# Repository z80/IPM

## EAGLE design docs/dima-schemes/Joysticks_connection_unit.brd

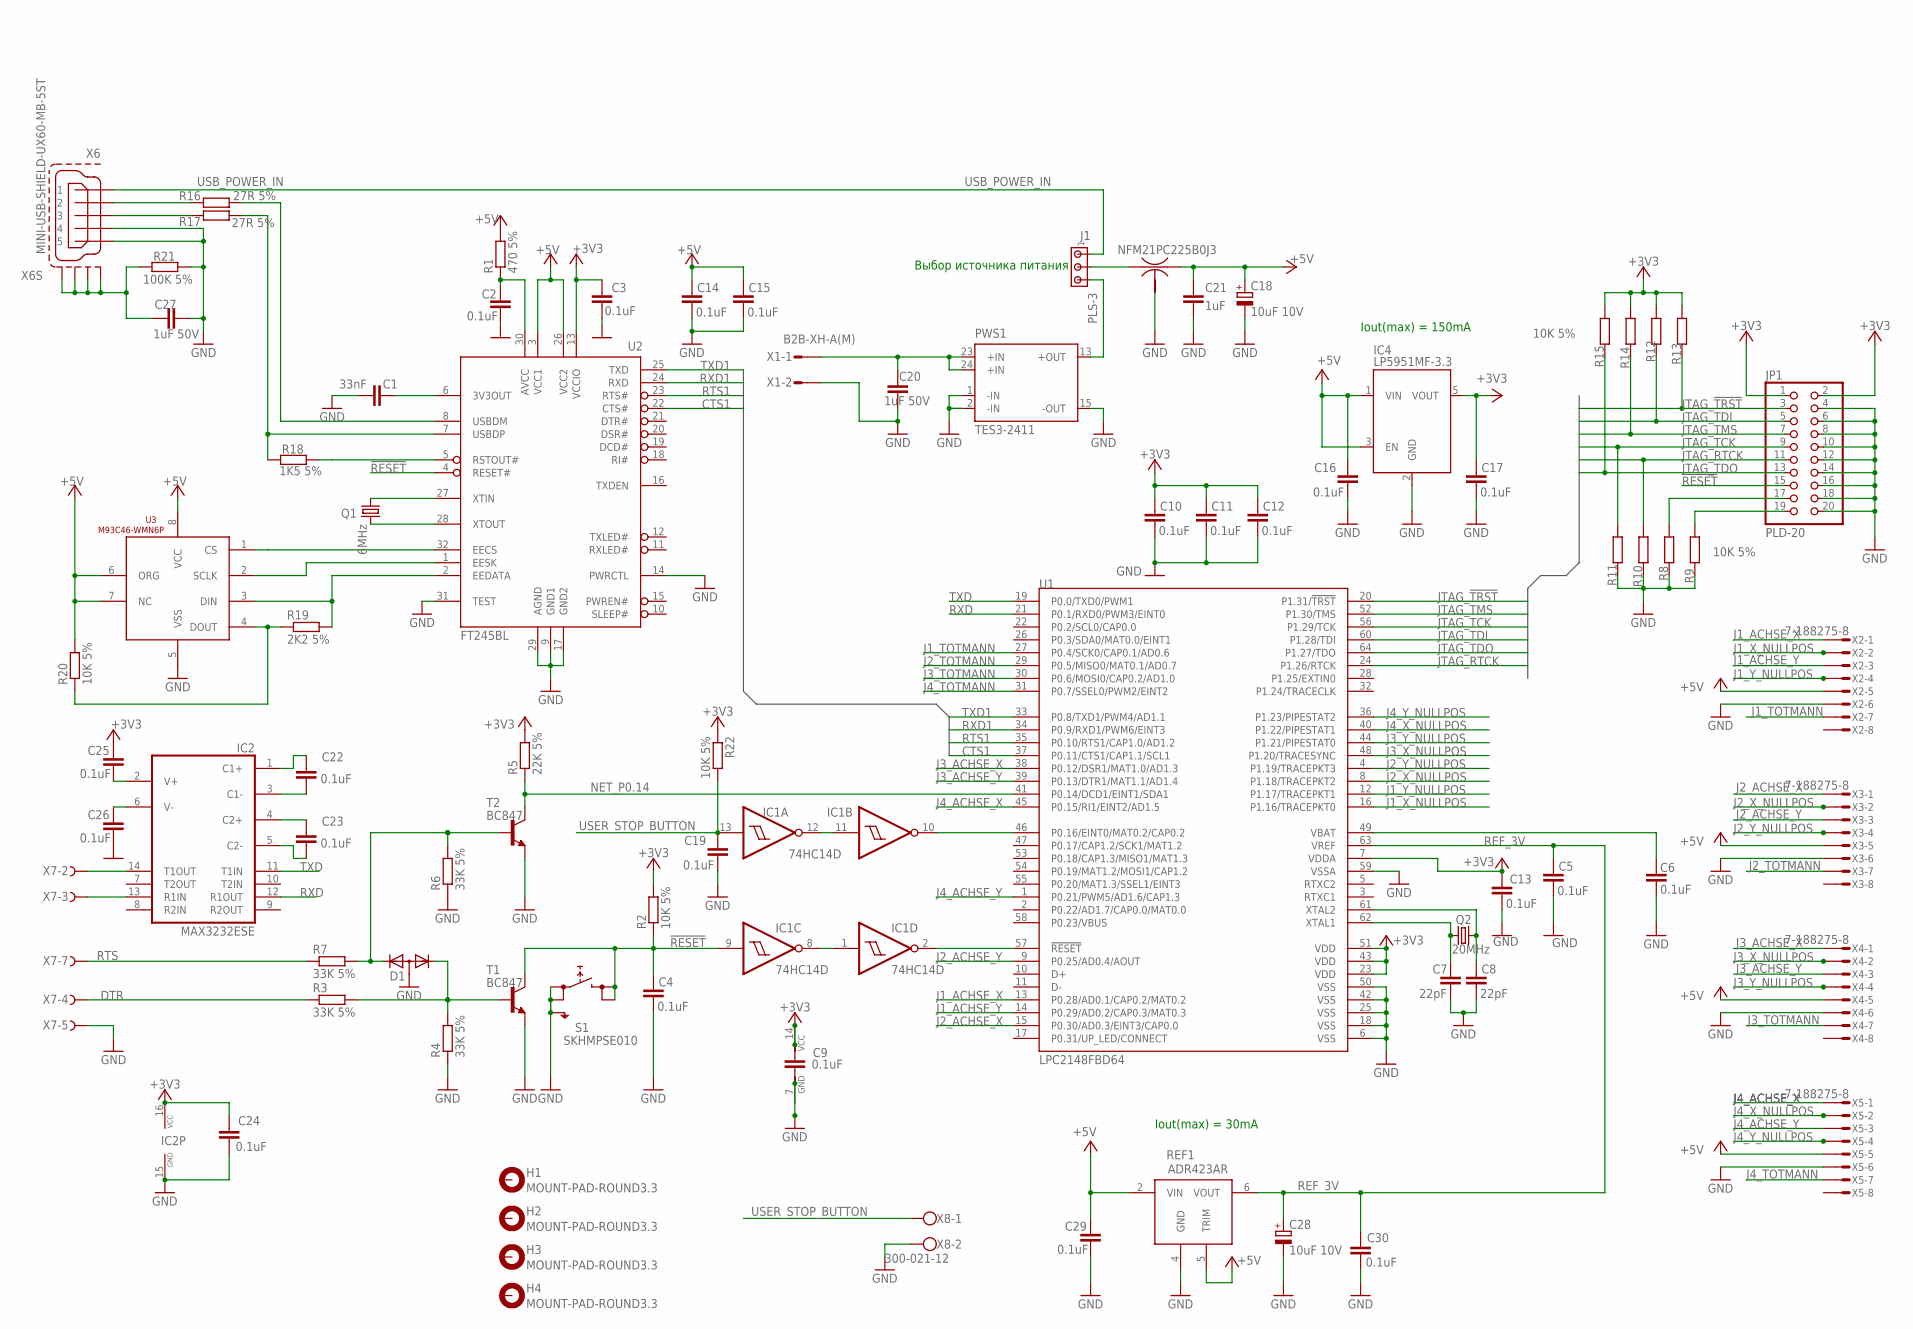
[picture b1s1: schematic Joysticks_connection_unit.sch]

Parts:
C1: 33nF; C0805
C2, C3, C4, C5, C6, C9, C10, C11, C12, C13, C14, C15, C16, C17, C19, C22, C23, C24, C25, C26, C29, C30: 0.1uF; C0805
C7, C8: 22pF; C0805
C18, C28: 10uF 10V; SMC_B
C20, C27: 1uF 50V; C0805
C21: 1uF; C0805
CF1: NFM21PC225B0J3; NFM21C
D1: DIODE-2CA|ACSOT23; SOT23
H1, H2, H3, H4: MOUNT-PAD-ROUND3.3; 3,3-PAD
IC1: 74HC14D; SO14
IC2: MAX3232ESE; SO16
IC4: LP5951MF-3.3; SOT23-5(MF05A)
J1: PLS-3; 10X03MTA
JP1: PLD-20; 2X10
PWS1: TES3-2411; TES3
Q1: 6MHz; HC49/S
Q2: 20MHz; HC49/S
R1: 470 5%; R0805
R2, R8, R9, R10, R11, R12, R13, R14, R15, R20, R22: 10K 5%; R0805
R3, R4, R6, R7: 33K 5%; R0805
R5: 22K 5%; R0805
R16, R17: 27R 5%; R0805
R18: 1K5 5%; R0805
R19: 2K2 5%; R0805
R21: 100K 5%; R0805
REF1: ADR423AR; SOIC8
S1: SKHMPSE010; SKHMPXE010
T1, T2: BC847; SOT23
U1: LPC2148FBD64; TSQFP50P1200X1200X160-64N
U2: FT245BL; LQFP32
U3: M93C46-WMN6P; SO8
X1: B2B-XH-A(M); B2B-XH-AM
X2, X3, X4, X5: 7-188275-8; MMT-F-SMD-8
X6: MINI-USB-SHIELD-UX60-MB-5ST; UX60-MB-5ST
X7: F09VPS; F09VP
X8: 300-021-12; W237-102

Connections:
!RESET: C4.1, IC1.9 (I), JP1.15, R2.1, S1.3 (2.1), S1.4 (2.2), T1.3 (C), U2.4 (RESET#)
+3V3: C3.1, C9.1, C10.1, C11.1, C12.1, C13.1, C17.1, C24.1, C25.1, IC1.14 (VCC), IC2.16 (VCC), IC4.5 (VOUT), JP1.1, JP1.2, R2.2, R5.2, R12.2, R13.2, R14.2, R15.2, R22.1, U1.7 (VDDA), U1.23 (VDD), U1.43 (VDD), U1.51 (VDD), U2.13 (VCCIO)
+5V: C14.1, C15.1, C16.1, C18.+, C21.1, C29.1, CF1.3, IC4.1 (VIN), IC4.3 (EN), R1.2, R20.2, REF1.2 (VIN), REF1.5 (TRIM), U2.3 (VCC1), U2.26 (VCC2), U3.6 (ORG), U3.7 (NC), U3.8 (VCC), X2.5, X3.5, X4.5, X5.5
CTS1: U1.37 (P0.11/CTS1/CAP1.1/SCL1), U2.22 (CTS#)
DTR: R3.1, X7.4
GND: C1.2, C2.2, C3.2, C4.2, C5.2, C6.2, C7.2, C8.2, C9.2, C10.2, C11.2, C12.2, C13.2, C14.2, C15.2, C16.2, C17.2, C18.-, C19.2, C20.2, C21.2, C24.2, C26.2, C27.2, C28.-, C29.2, C30.2, CF1.2@1 (2), D1.3 (A), IC1.7 (GND), IC2.15 (GND), IC4.2 (GND), JP1.4, JP1.6, JP1.8, JP1.10, JP1.12, JP1.14, JP1.16, JP1.18, JP1.20, PWS1.1 (-IN), PWS1.2 (-IN), PWS1.15 (-OUT), R4.1, R6.1, R8.1, R9.1, R10.1, R11.1, R21.2, REF1.4 (GND), S1.1 (1.1), S1.2 (1.2), S1.5 (SH), T1.2 (E), T2.2 (E), U1.6 (VSS), U1.18 (VSS), U1.25 (VSS), U1.42 (VSS), U1.50 (VSS), U1.59 (VSSA), U2.9 (GND1), U2.14 (PWRCTL), U2.17 (GND2), U2.29 (AGND), U2.31 (TEST), U3.5 (VSS), X1.2, X2.6, X3.6, X4.6, X5.6, X6.4, X6.5, X7.5, X8.2
J1_ACHSE_X: U1.13 (P0.28/AD0.1/CAP0.2/MAT0.2), X2.1
J1_ACHSE_Y: U1.14 (P0.29/AD0.2/CAP0.3/MAT0.3), X2.3
J1_TOTMANN: U1.27 (P0.4/SCK0/CAP0.1/AD0.6), X2.7
J1_X_NULLPOS: U1.16 (P1.16/TRACEPKT0), X2.2
J1_Y_NULLPOS: U1.12 (P1.17/TRACEPKT1), X2.4
J2_ACHSE_X: U1.15 (P0.30/AD0.3/EINT3/CAP0.0), X3.1
J2_ACHSE_Y: U1.9 (P0.25/AD0.4/AOUT), X3.3
J2_TOTMANN: U1.29 (P0.5/MISO0/MAT0.1/AD0.7), X3.7
J2_X_NULLPOS: U1.8 (P1.18/TRACEPKT2), X3.2
J2_Y_NULLPOS: U1.4 (P1.19/TRACEPKT3), X3.4
J3_ACHSE_X: U1.38 (P0.12/DSR1/MAT1.0/AD1.3), X4.1
J3_ACHSE_Y: U1.39 (P0.13/DTR1/MAT1.1/AD1.4), X4.3
J3_TOTMANN: U1.30 (P0.6/MOSI0/CAP0.2/AD1.0), X4.7
J3_X_NULLPOS: U1.48 (P1.20/TRACESYNC), X4.2
J3_Y_NULLPOS: U1.44 (P1.21/PIPESTAT0), X4.4
J4_ACHSE_X: U1.45 (P0.15/RI1/EINT2/AD1.5), X5.1
J4_ACHSE_Y: U1.1 (P0.21/PWM5/AD1.6/CAP1.3), X5.3
J4_TOTMANN: U1.31 (P0.7/SSEL0/PWM2/EINT2), X5.7
J4_X_NULLPOS: U1.40 (P1.22/PIPESTAT1), X5.2
J4_Y_NULLPOS: U1.36 (P1.23/PIPESTAT2), X5.4
JTAG_!TRST: JP1.3, R13.1, U1.20 (P1.31/!TRST)
JTAG_RTCK: JP1.11, R10.2, U1.24 (P1.26/RTCK)
JTAG_TCK: JP1.9, R11.2, U1.56 (P1.29/TCK)
JTAG_TDI: JP1.5, R12.1, U1.60 (P1.28/TDI)
JTAG_TDO: JP1.13, R15.1, U1.64 (P1.27/TDO)
JTAG_TMS: JP1.7, R14.1, U1.52 (P1.30/TMS)
unnamed: C2.1, R1.1, U2.30 (AVCC)
unnamed: C1.1, U2.6 (3V3OUT)
unnamed: IC1.1 (I), IC1.8 (O)
unnamed: JP1.19, R9.2
unnamed: C20.1, PWS1.23 (+IN), PWS1.24 (+IN), X1.1
unnamed: C6.1, U1.49 (VBAT)
unnamed: D1.1 (K1), R3.2, R4.2, T1.1 (B)
unnamed: JP1.17, R8.2
unnamed: C7.1, Q2.1, U1.62 (XTAL1)
unnamed: C8.1, Q2.2, U1.61 (XTAL2)
unnamed: Q1.2, U2.28 (XTOUT)
unnamed: Q1.1, U2.27 (XTIN)
unnamed: R16.1, X6.2
unnamed: R17.1, X6.3
unnamed: R17.2, R18.1, U2.7 (USBDP)
unnamed: R16.2, U2.8 (USBDM)
unnamed: R18.2, U2.5 (RSTOUT#)
unnamed: U2.32 (EECS), U3.1 (CS)
unnamed: U2.1 (EESK), U3.2 (SCLK)
unnamed: R19.2, U2.2 (EEDATA), U3.3 (DIN)
unnamed: R19.1, R20.1, U3.4 (DOUT)
unnamed: J1.3, PWS1.13 (+OUT)
unnamed: IC1.11 (I), IC1.12 (O)
unnamed: IC1.2 (O), U1.57 (!RESET)
unnamed: IC1.10 (O), U1.46 (P0.16/EINT0/MAT0.2/CAP0.2)
unnamed: CF1.1, J1.2
unnamed: C22.2, IC2.3 (C1-)
unnamed: C22.1, IC2.1 (C1+)
unnamed: C23.1, IC2.4 (C2+)
unnamed: C23.2, IC2.5 (C2-)
unnamed: C25.2, IC2.2 (V+)
unnamed: C26.1, IC2.6 (V-)
unnamed: IC2.14 (T1OUT), X7.2
unnamed: IC2.13 (R1IN), X7.3
unnamed: D1.2 (K2), R6.2, R7.2, T2.1 (B)
unnamed: C27.1, R21.1, X6.M1 (S1), X6.M2 (S2), X6.M3 (S3), X6.M4 (S4)
NET_P0.14: R5.1, T2.3 (C), U1.41 (P0.14/DCD1/EINT1/SDA1)
REF_3V: C5.1, C28.+, C30.1, REF1.6 (VOUT), U1.63 (VREF)
RTS: R7.1, X7.7
RTS1: U1.35 (P0.10/RTS1/CAP1.0/AD1.2), U2.23 (RTS#)
RXD: IC2.12 (R1OUT), U1.21 (P0.1/RXD0/PWM3/EINT0)
RXD1: U1.34 (P0.9/RXD1/PWM6/EINT3), U2.24 (RXD)
TXD: IC2.11 (T1IN), U1.19 (P0.0/TXD0/PWM1)
TXD1: U1.33 (P0.8/TXD1/PWM4/AD1.1), U2.25 (TXD)
USB_POWER_IN: J1.1, X6.1
USER_STOP_BUTTON: C19.1, IC1.13 (I), R22.2, X8.1

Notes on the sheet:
Iout(max) = 150mA
Выбор источника питания
Iout(max) = 30mA

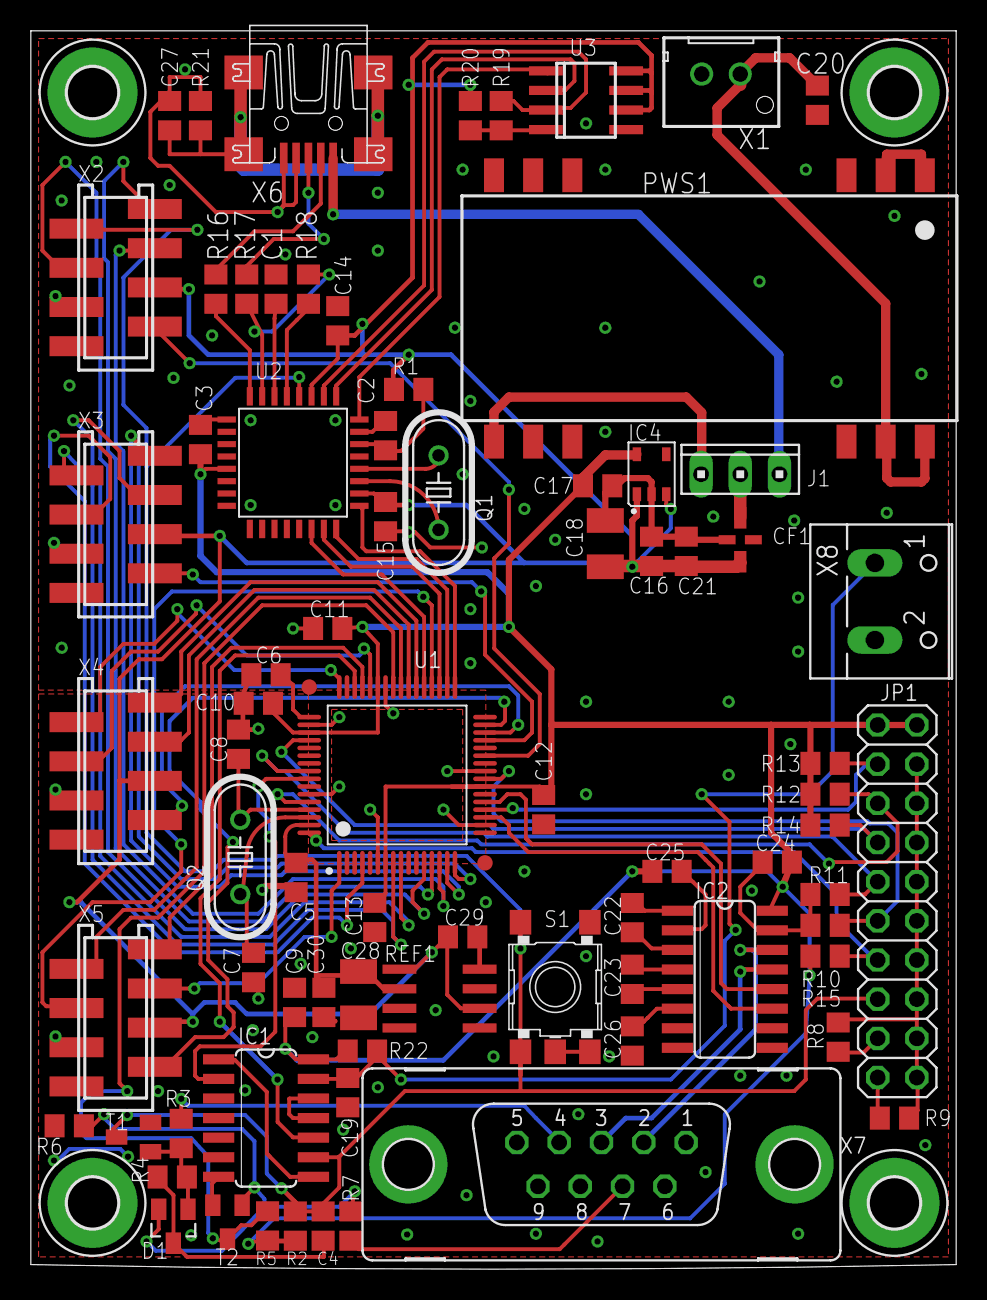
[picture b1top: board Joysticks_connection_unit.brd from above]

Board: 2 copper layers, 60.0 x 80.3 mm, 81 parts (0 on the bottom side), 78 nets.

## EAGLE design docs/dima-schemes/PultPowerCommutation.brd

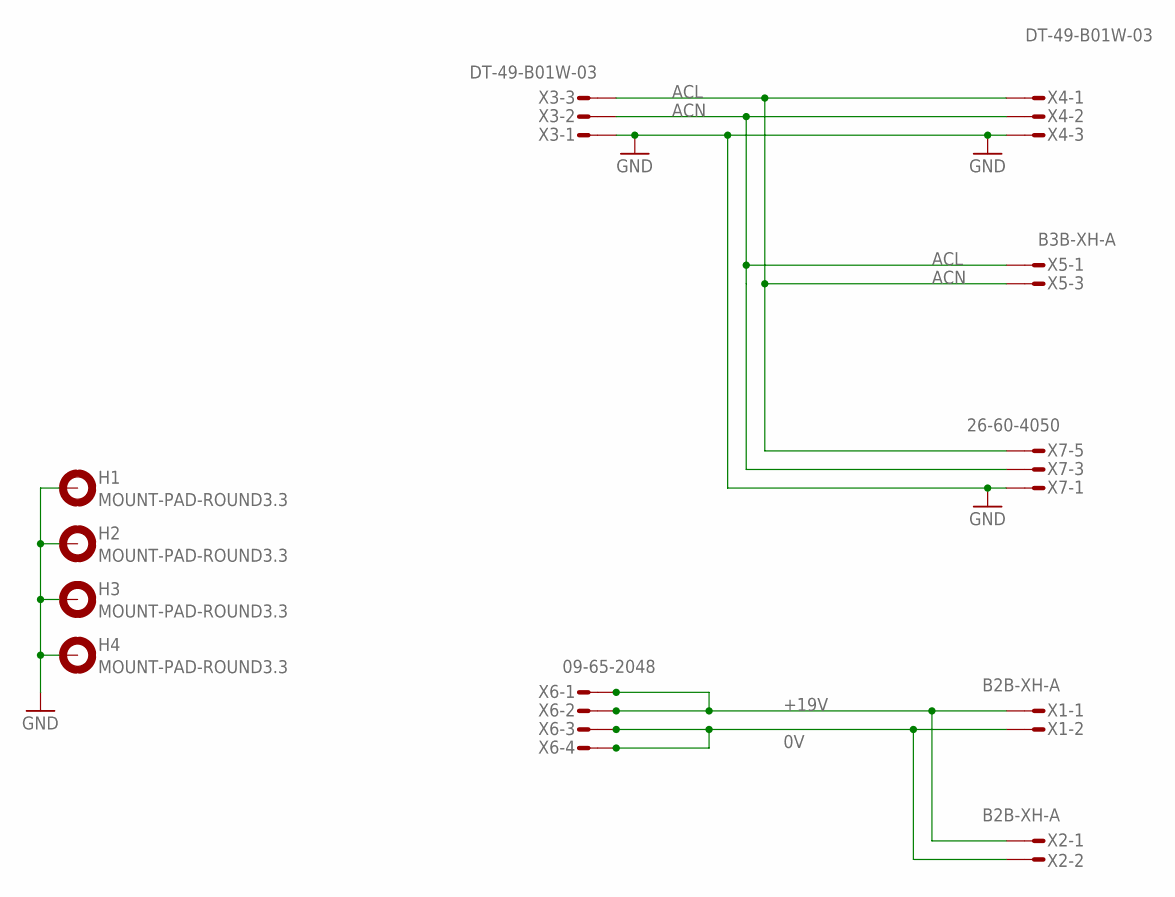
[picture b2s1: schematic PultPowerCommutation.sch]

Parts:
H1, H2, H3, H4: MOUNT-PAD-ROUND3.3; 3,3-PAD
X1, X2: B2B-XH-A; B2B-XH-AM
X3, X4: DT-49-B01W-03; DINKLE_DT-49-B01W-03
X5: B3B-XH-A; B3B-XH-AM
X6: 09-65-2048; MOLEX_09-65-2048
X7: 26-60-4050; MOLEX_26-60-4050

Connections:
0V: X1.2, X2.2, X6.3, X6.4
+19V: X1.1, X2.1, X6.1, X6.2
ACL: X3.3, X4.1, X5.3, X7.5
ACN: X3.2, X4.2, X5.1, X7.3
GND: H1.B3,3, H2.B3,3, H3.B3,3, H4.B3,3, X3.1, X4.3, X7.1

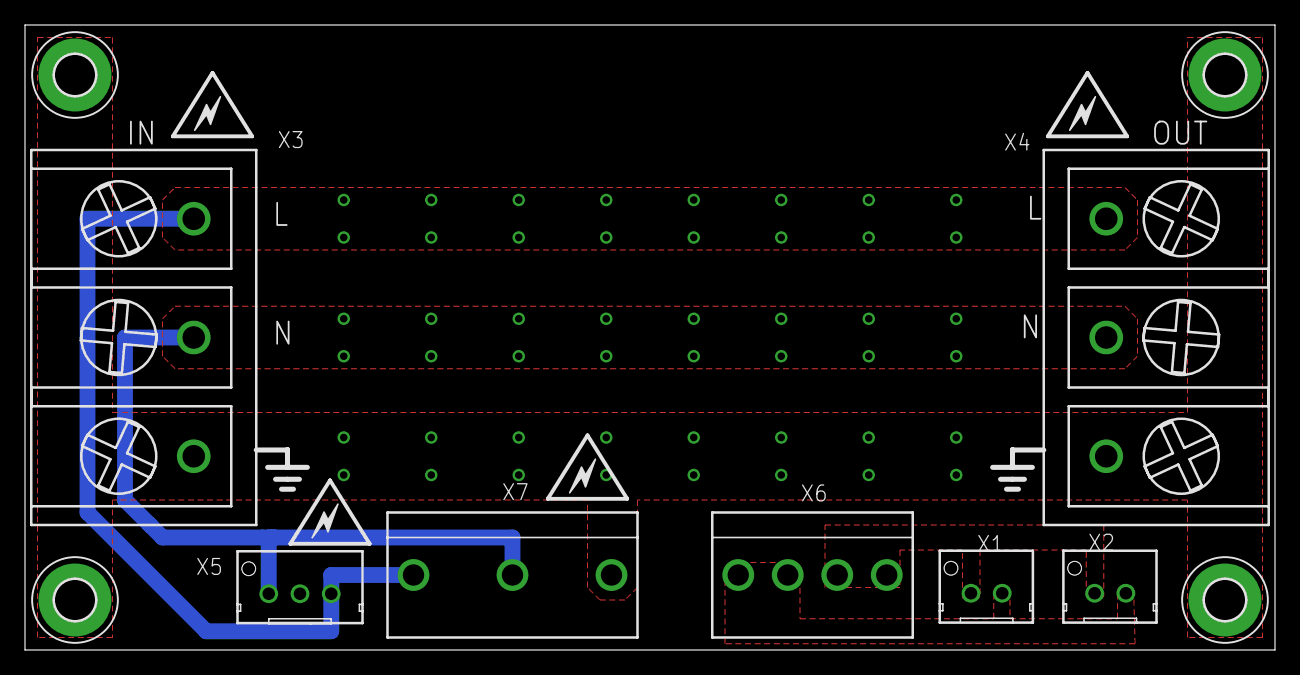
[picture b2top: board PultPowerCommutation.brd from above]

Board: 2 copper layers, 100.0 x 50.0 mm, 17 parts (0 on the bottom side), 5 nets.

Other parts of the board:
U$1, U$2, U$3, U$4: ICON_BOLT-S
U$5, U$10: ICON_GND2

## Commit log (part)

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2012-11-16 USB doesn't work from scratch. Debugging...
2012-11-16 Ignoring additional folders.
2012-11-16 Regular USB example works. It looks I have to play starting from it adding necessary functionality.
2012-11-18 Set maximum frequency.
2012-11-18 USB is recognized.
2012-11-18 Taken chibios from repository's stable branch. But it doesn't help. i2cStart() hangs MCU up.
2012-11-18 It seems original I2C example doesn't hang up.
2012-11-18 Should be tested but i2c slave functions should be recovered.
2012-11-18 USB write works but nothing is returned back.
2012-11-19 Renamed slave functions into just one and named it i2cSlaveIoTimeout().
2012-11-19 Moved CPAL content to a separate directory.
2012-11-19 Trying to implement I2C slave mode. Most probably I need remake appropriate interrupt service routines in i2c_lld.c according to examples.
2012-11-20 Only another DB-37 suits size. Also should think for a while about rebolving motor encoder's socket.
2012-11-20 Schema edited. Have to leave just tow manipulator controls on one board. So it will be two boards for total control. Painted PCB edge with placment holes identical to previous valve_2 PCB.
2012-11-21 Placing elements.
2012-11-21 All components are within board perimeter.
2012-11-21 Schematic wasn't actually changed. It looks like just date inside of a file is different.
2012-11-22 Back imported semi routed board.
2012-11-22 Failed to route 2 wires. Just before imorting SES file.
2012-11-22 Before import SES file.
2012-11-22 Routed power for MCUs.
2012-11-22 Board with willed GND polygons.
2012-11-25 Debugging I2C.
2012-11-25 Trying to make IO with slave boards.
2012-11-25 Separated read and write queries. Bot returned value is not 0xFFFFFFFF but it is not 0 as well :(
2012-11-25 Commented out test I2C constant return.
2012-11-26 Software remote control project is imported from robocam project.
2012-11-28 xmpp
2012-11-28 Fixed send file button. Added help button.
2012-11-28 Corrected joystick ranges.
2012-11-29 Fixed help system.
2012-11-29 Turning off unused Qt modules.
2012-11-29 Learning LibreCAD.
2012-12-01 Drawing. Looks like mentioned all cable types. Made all of them at least 1m long to provide ability to connect the most distant points.
2012-12-03 Scheme for 50 in progress.
2012-12-04 Added output 220VAC wire.
2012-12-05 Finished bill of materials.
2012-12-08 Added circles but didn't cut off lines with those circles intersections.
2012-12-08 Shemes for both 50 and 1.5. And sockets different from 50 added to sockets list.
2012-12-10 Cables file is renamed.
2012-12-10 routing...
2012-12-10 so-8 package is replaced with msop-8 for ad5300 8-bit spi dac chip.
2012-12-11 Gerber files are prepared. Reference frame zero point is put close to a board corner.
2012-12-16 Designing drawings...
2012-12-18 Annotated last scheme for robot "50".
2012-12-21 Annotation is done. Or at least is seems to me it is done.
2012-12-22 Made little note for the future.
2012-12-24 Turned off output permit. It caused Power voltage to be on a normal level of 5.2V. Otherwise it is 2.7V. It sools like
2012-12-24 Test application for testing inputs.
2012-12-24 Returned output on by default.
2012-12-24 Increased I2C query period.
2012-12-24 Read should be more correct. But can't check because USB device doesn't work!
2012-12-24 When read routine is dummy USB works very well!
2012-12-26 In the case of failure I2C should be resurrected by using i2cStart() routine. And changed board file and directory!
2012-12-28 Led widget.
2012-12-28 Removed image files.
2012-12-28 Valve test window development.
2012-12-30 Removed unnecessary includes in header file.
2012-12-30 Adjusted INI files for local work.
2012-12-30 Implemented MCU control routine.
2012-12-30 Provided access to mcu variable from the outside.
2012-12-30 Made read time delays 1 microsecond. Added L293DD's out_enable turn on/off depending on values. Read, write and I2C IO only when necessary.
2012-12-31 Removed unused class.
2013-01-02 I2C stopped working.
2013-01-02 Playing with reading.
2013-01-03 Played with I2C and it's BUSY flag in slave mode. In the case of timeout with BUSY being for too long it is signaled to calling thread as returned RDY_TIMEOUT result.
2013-01-03 Compiled code.
2013-01-03 Returned the state when it worked. And it works!!!
2013-01-03 Returned back little improvement. I2C still works.
2013-01-03 Introduced separate sleep intervals for master and slave modes.
2013-01-03 Inserted condition defines.
2013-01-03 Increased I2C slave interval up to 20 milliseconds.
2013-01-03 Decreased I2C master period to 20 milliseconds. It looks like work is stable.
2013-01-03 Changed boards count. Now there are 3 boards. 1 master and 2 slaves.
2013-01-04 Watchdog works!
2013-01-04 USB on/off pin was input with internal pullup. Changed to be output pushpull.
2013-01-04 Changed boards number. Implemented report() function. But something is wrong.
2013-01-04 Found posible trouble...
2013-01-04 Fixed error associated with master board outputs.
2013-01-06 Just test firmware to make sure MCU is alive.
2013-01-13 Added moto1 and moto2 intermediate files into ignore list.
2013-01-13 LEDs initialization added.
2013-01-13 Moto2 compiles.
2013-01-15 BMSD control functions compile without errors.
2013-01-16 In this configuration LEDs work.
2013-01-16 In such configuration it hangs up.
2013-01-16 LockI/UnlockI in timer callback is bad.
2013-01-17 Router drawing.
2013-01-17 Relative encoders capture implemented. But not tested yet as well as absolute one.
2013-01-19 Fixed a few issues in bmsd_ctrl.c file.
2013-01-19 Partially written I2C IO. Starting exec_ctrl...
2013-01-19 Removed unnecessary files.
2013-01-19 Started generic I2C io.
2013-01-20 Recovered LEDs thread.
2013-01-20 Added new commands to mcuctrl. luamcuctrl is pending...
2013-01-20 Aded LEDs I2C test command. It will be the very first issue to test!
2013-01-21 Added watchdog initialization. Removed debug UART io thread.
2013-01-21 Made fixed slave address. Increased IO buffers on master side.
2013-01-21 Correct I2C slave io result.
2013-01-21 Turn hardware on step by step...
2013-01-21 Interrupt driven I2C slave. Master reports about successful write result.
2013-01-21 Still goes well. But have to off/on boards to recover IO.
2013-01-21 Command to turn LED-1 on passed!!!
2013-01-22 Turned off debug LED command invocation.
2013-01-22 UART is excluded by I2C. Whey don't work simultaneously. Only one of them.
2013-01-22 Error is caused by using one and the same DMA channels for UART2 and I2C1. It looks like should try Serial instead.
2013-01-22 Turned compile optimization on. Not sure about if it works or not but LEDs still blink...
2013-01-22 Now I see blinking! Just forgotten to insert callbacks invocation.
2013-01-22 Fixed a few obvious errors. But it looks like execPostCmd() hangs io up.
2013-01-22 USB command has reached moto_ctrl board through I2C.
2013-01-26 Designing and checking moto1 project.
2013-01-26 Made I2C address according to mainstream. E.i. 64 + 2*ind+1 for moto1 and 64+ 2*ind for moto2.
2013-01-26 Removed reference to original example.
2013-01-28 iwdgReset() without initializing IWDG caused MCU hang up.
2013-01-28 Reading I2C through USB causes reading MCU hang up. Debugging this phenomena.
2013-01-28 I2C debug in progress.
2013-01-28 In slave mode AF is not an error!!!
2013-01-28 Rebuilt moto1 and moto2. Placed IWDG reset to main loop.
2013-01-29 Added LSM303 to host.lua.
2013-01-29 Accelerometer class development...
2013-01-30 Made usb_io to wait for "<\r\n" combination.
2013-01-30 New way of transfer end recognition works. E.i. all MCU replies end with "<\r\n". And pattern search is made with boost::regex_search().
2013-01-30 Corrent data readout.
2013-01-30 Accelerometer control functions are inserted into mmcuctrl library and to luamcuctrl Lua module.
2013-02-12 Assembling and soldering procedure.
2013-02-14 Fixed errors caused by accelerometer development.
2013-02-14 Moved XMPP server to host side.
2013-02-14 Commented out debug print( "here" ) invocation. It works properly.
2013-02-14 reportInputs() function added. But isn't checked!!!
2013-02-18 valveTest() routine for testing output(s).
2013-02-22 Made dsiplay( ... ) function for sending reports about variables in text format.
2013-02-22 First byte doesn't participate to crc calculation.
2013-02-24 Switch to output is made beforehand. And some delay is provided before back switch to input.
2013-02-24 Bits mirroring routine.
2013-02-24 Checked CRC calculation. Seems it matches with Lua implementation.
2013-02-25 Added BMSD:enumCrc() routine.
2013-02-26 Commands modified. BMSD:start() and BMSD:stop() do change LED state but don't change motor. After start/stop button click motor starts. And speed/dir commands work. But can't make it work without but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
2013-02-28 Modified BMSD status cmd.
2013-03-05 ESCON Lua control module.
2013-03-09 Added move() method to ESCON class.
2013-03-15 Added Pawn. Playing around...
2013-03-15 To build proper main.amx it is necessary to use "-S1024 -XD10240" flags to "pawncc" command.
2013-03-16 Pawn test chaned. Added compile script.
2013-03-22 Looks like ROM located instructions works!
2013-03-31 FTDI support compiles somehow. But it doesn't mean it works.
2013-04-09 Documentation for LPC214x. Implemented joystick controls. FTDI should be remade for FT232BL.
2013-04-13 Changed scheme for easier routing.
2013-04-13 Zones doesn't work in the new KiCad version 2013-03-19.
2013-04-17 Changed to FT232BL.
2013-04-18 Made test firmware.
2013-04-18 Found a project with all peripherials of LPC2148.
2013-04-18 Filled UART1. Should be checked.
2013-04-18 Removed temporary files.
2013-04-19 UART1 transmit works.
2013-04-19 Involved ADC init and GPIO init. It's alive. But if ADC read finish loop is involved it never leaves this loop.
2013-04-19 Don't hang up. Strange changed j[2].value[0] to local variable and it stopped hanging up at this point.
2013-04-19 And now all ADC channels work. I changed frequency divider in ADC CR register. Now ADC frequency is 20Mhz/5 = 4MHz.
2013-04-19 Tried sending string to get it with Putty. But failed. Tried sending 0x00 to measure real baudrate. Got approximately 40000. To it is very likely that it's 38400.
2013-04-19 Implemented FTDI test for Windows.
2013-04-19 Added timeout and putting RTS low.
2013-04-20 Device could be opened but serial number request fails. Baud rate set fails. So It's impossible to work with the device.
2013-04-21 Remade using native COM port functionality.
2013-04-22 Commented out test functionality and uncommented work functionality.
2013-04-23 Remade JoyCtrl::query() to return read buffer after quering state. Now it doesn't work in Linux.
2013-04-23 Serial port for Qt library.
2013-04-24 PAcked struct to ocupy exactly as much space as necessary.
2013-04-25 Inserted joystick processing functionality for debugging.
2013-04-25 ADC value seems to be normal only for the very first ADC, For last three it is with reversed bytes order. Made all to be the same. But should check that!
2013-04-26 Fixed open() state in the case of open() failure.
2013-04-26 Joystick datasheet.
2013-05-15 Unmodified ref-frame calculation algorithm.
2013-05-15 Limitation is alpha1+alpha2=0.
2013-06-13 Modifying prices table.
2013-08-05 "Pult" power supply datasheets.
2013-10-31 Acceptance questions.
2013-11-14 Debugging an algorithm.
2013-11-14 With spin it also runs.
2013-11-16 Configured movements according to experiments.
2013-11-18 Movement step output.
2013-11-18 Initial state.
2013-11-18 Both movements without sensors work. Spinning works.
2013-11-18 Movement for 50 initial.
2013-11-21 Switched to "1.5".
2013-12-02 Have QR decoding for lowest and medium error correction values.
2013-12-03 Modified paper find procedure. Added squares example as is.
2013-12-03 Moving qr corners extraction to a separate class.
2013-12-04 Reading works but not always.
2013-12-04 More to calibration.
2013-12-11 Started manipulator processing.
2013-12-18 Motor datasheet.
2013-12-19 Just a debug line.
2014-02-27 Set IP address of the robot.
2014-02-27 Movement joystich is processed properly.
2014-05-09 Made displaying video using libvlc.
2014-05-22 End sensors are involved into algorithm.
2015-03-31 Added bigger delays.
2015-04-06 Made absolute encoder handling tunable.

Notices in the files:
parts and their libraries:
philips-5: Copyright 2006 Weartronics
dicons: Copyright (C) 2004, Bob Starr (rtzaudio@mindspring.com)
